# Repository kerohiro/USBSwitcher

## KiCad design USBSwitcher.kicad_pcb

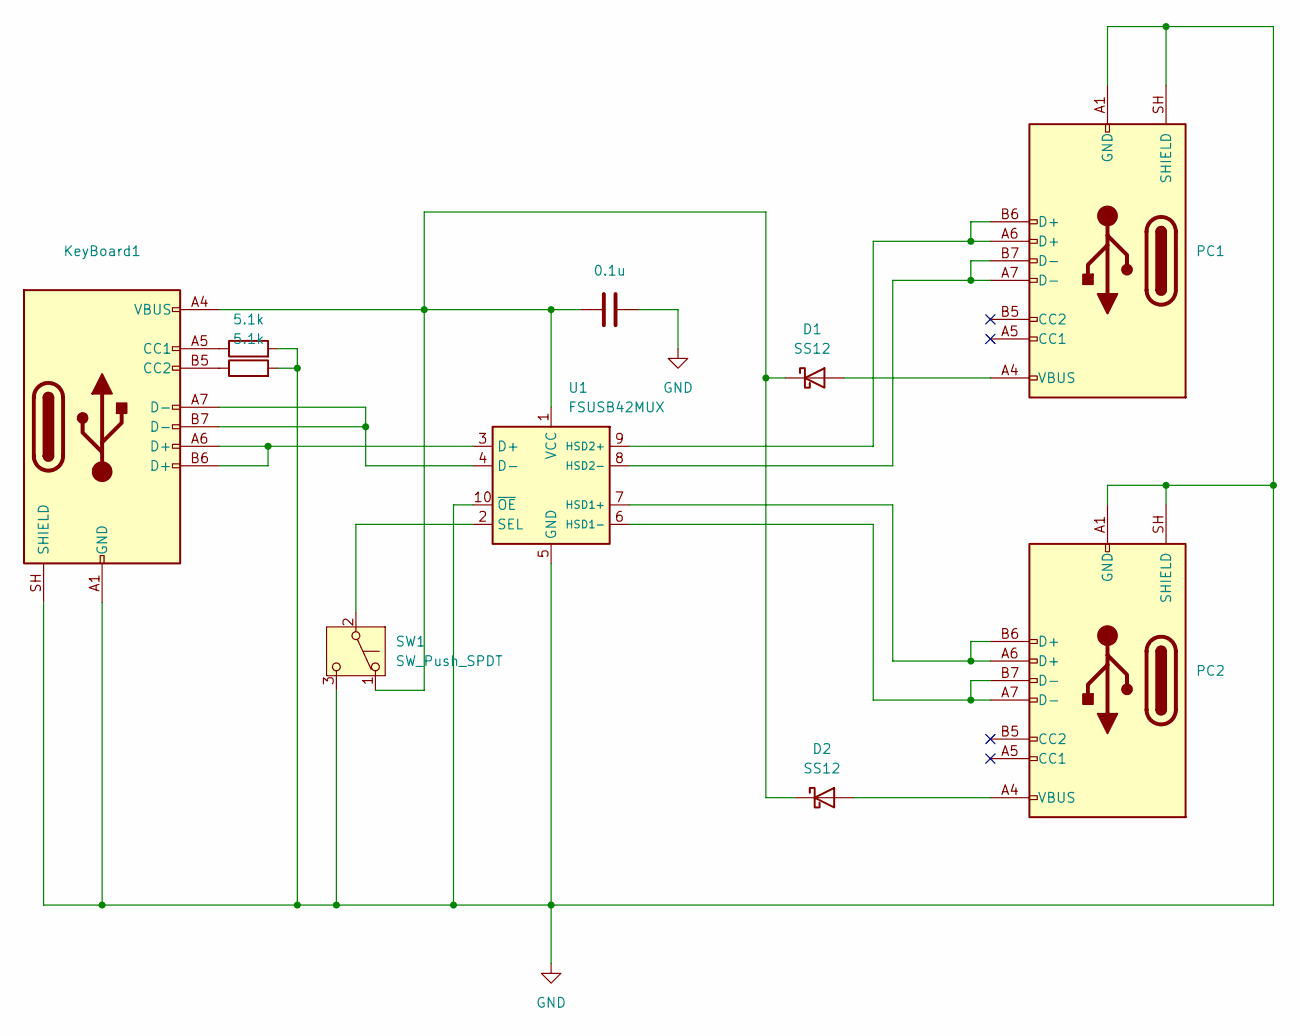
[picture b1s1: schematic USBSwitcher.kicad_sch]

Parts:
C1: 0.1u; C_0201_0603Metric
D1, D2: SS12; D_SMA
KeyBoard1: USB_C_Receptacle_USB2.0_14P; USB_C_Receptacle_GCT_USB4085
PC1, PC2: USB_C_Receptacle_USB2.0_14P; USB_C_Receptacle_GCT_USB4085
R1, R2: 5.1k; R_0201_0603Metric
SW1: SW_Push_SPDT; SW_Push_1P2T_Vertical_E-Switch_800UDP8P1A1M6
U1: FSUSB42MUX; MSOP-10_3x3mm_P0.5mm

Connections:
GND: C1.2, KeyBoard1.A1 (GND), KeyBoard1.A12 (GND), KeyBoard1.B1 (GND), KeyBoard1.B12 (GND), KeyBoard1.SH (SHIELD), PC1.A1 (GND), PC1.A12 (GND), PC1.B1 (GND), PC1.B12 (GND), PC1.SH (SHIELD), PC2.A1 (GND), PC2.A12 (GND), PC2.B1 (GND), PC2.B12 (GND), PC2.SH (SHIELD), R1.2, R2.2, SW1.3 (C), U1.5 (GND), U1.10 (~OE)
unnamed: D1.2 (A), PC1.A4 (VBUS), PC1.A9 (VBUS), PC1.B4 (VBUS), PC1.B9 (VBUS)
unnamed: C1.1, D1.1 (K), D2.1 (K), KeyBoard1.A4 (VBUS), KeyBoard1.A9 (VBUS), KeyBoard1.B4 (VBUS), KeyBoard1.B9 (VBUS), SW1.1 (A), U1.1 (VCC)
unnamed: D2.2 (A), PC2.A4 (VBUS), PC2.A9 (VBUS), PC2.B4 (VBUS), PC2.B9 (VBUS)
unnamed: KeyBoard1.A5 (CC1), R1.1
unnamed: KeyBoard1.B5 (CC2), R2.1
unnamed: SW1.2 (B), U1.2 (SEL)
unnamed: KeyBoard1.A6 (D+), KeyBoard1.B6 (D+), U1.3 (D+)
unnamed: KeyBoard1.A7 (D-), KeyBoard1.B7 (D-), U1.4 (D-)
unnamed: PC2.A6 (D+), PC2.B6 (D+), U1.7 (HSD1+)
unnamed: PC2.A7 (D-), PC2.B7 (D-), U1.6 (HSD1-)
unnamed: PC1.A6 (D+), PC1.B6 (D+), U1.9 (HSD2+)
unnamed: PC1.A7 (D-), PC1.B7 (D-), U1.8 (HSD2-)

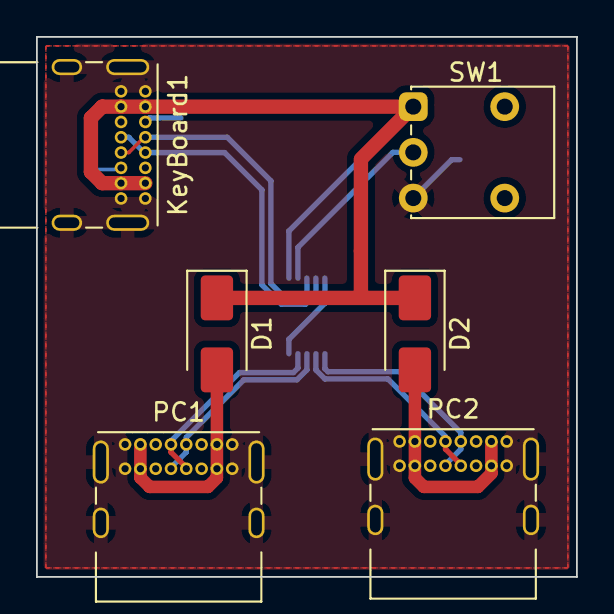
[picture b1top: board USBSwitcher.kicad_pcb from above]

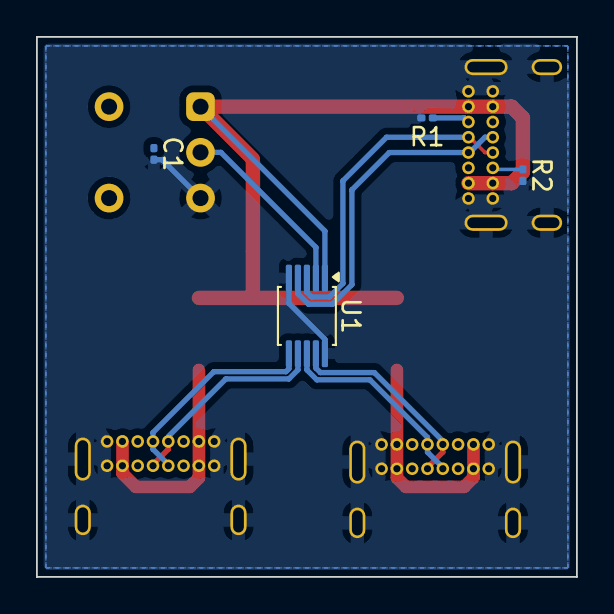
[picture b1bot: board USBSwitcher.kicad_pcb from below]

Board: 2 copper layers, 30.0 x 30.0 mm, 10 parts (4 on the bottom side), 13 nets.
